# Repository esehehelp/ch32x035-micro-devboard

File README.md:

# CH32X035F7P6 Micro Devboard

CH32X035F7P6 (RISC-V, 48 MHz, 62 KB flash, 20 KB RAM) の小型開発ボード。

## 概要

USB CDC-ACM ライブラリ (`ch32x-cdc`) を中心に、PlatformIO と Arduino IDE の両方をサポート。
ESP32/RP2040 の Arduino Serial と同じ体験 — 初期化を呼ぶだけで USB シリアルが使え、1200bps タッチでファームウェア更新ができる。

## PlatformIO (firmware/)

### 構成

```
firmware/
  platformio.ini          # PlatformIO 設定
  ch32_1k2touch.py        # カスタムアップロードスクリプト
  src/
    main.c                # サンプルアプリ (PC3 blink + CDC echo)
    startup.S             # ベクタテーブル + 起動コード
    link.ld               # リンカスクリプト
  lib/
    ch32x-cdc/
      include/
        ch32x_cdc.h       # 公開 API
        ch32x_regs.h      # MIT レジスタ定義 (WCH HAL 非依存)
      src/
        ch32x_cdc.c       # CDC 実装 (ディスクリプタ, ISR, バッファ)
```

### ビルド & 書き込み

```bash
cd firmware

# ビルド
pio run

# 書き込み (初回: wch-link 経由)
pio run -t upload --upload-port wlink

# 書き込み (2回目以降: USB CDC 1200bps タッチ経由, wch-link 不要)
pio run -t upload
```

初回書き込みは wch-link (SWD) が必要。一度ファームウェアが動けば、以降は USB ケーブルだけで `pio run -t upload` でフラッシュできる。

## Arduino IDE (arduino/)

### インストール

1. `arduino/ch32x035f7p6/` を Arduino のハードウェアディレクトリにコピーまたはシンボリックリンク:
   ```bash
   # Linux
   ln -s $(pwd)/arduino/ch32x035f7p6 ~/.arduino15/packages/ch32x035f7p6

   # または Arduino IDE の「ファイル > 環境設定 > スケッチブックの保存場所」内の
   # hardware/ch32x035f7p6/ に配置
   ```
2. ツールチェイン: WCH の RISC-V GCC (`xpack-riscv-none-embed-gcc`) をパスに追加
3. ボード選択: **CH32X035F7P6** を選択
4. アップロード: 1200bps タッチ + wchisp による自動書き込み

### Arduino API サポート

- `Serial` — USB CDC シリアル (`USBSerial` クラス、`Print` 継承)
- `millis()` / `micros()` / `delay()` / `delayMicroseconds()` — SysTick ベース
- `pinMode()` / `digitalWrite()` / `digitalRead()`

### API

```c
#include "ch32x_cdc.h"

// 初期化 (NULL でデフォルト設定)
ch32x_cdc_config_t cfg = { .magic_baud_enable = 1 };
ch32x_cdc_init(&cfg);

// 読み込み
int ch32x_cdc_available(void);       // 受信バイト数
int ch32x_cdc_read(void);            // 1バイト読み込み (-1 = 空)
size_t ch32x_cdc_read_buf(buf, max); // バッファに一括読み込み

// 書き込み
size_t ch32x_cdc_write(buf, len);    // バイト列送信
size_t ch32x_cdc_print(str);         // 文字列送信
void ch32x_cdc_flush(void);          // TX 完了待ち

// BootROM へリブート (手動呼び出し用)
void ch32x_cdc_reboot_to_bootrom(void);
```

#### 設定

```c
typedef struct {
    int      magic_baud_enable;  // 1200bps リブートトリガ (デフォルト: 有効)
    uint32_t magic_baud;         // トリガボーレート (デフォルト: 1200)
    void (*pre_reboot)(void);    // リブート前コールバック
} ch32x_cdc_config_t;
```

#### RX コールバック

```c
// ISR コンテキストで呼ばれる (weak シンボル、アプリ側でオーバーライド可)
void ch32x_cdc_on_rx(const uint8_t *buf, size_t len) {
    // 受信データを処理
}
```

### サンプルアプリ (PlatformIO)

`firmware/src/main.c` — PC3 LED 点滅 (500ms) + USB CDC エコー。

```c
#include "ch32x_regs.h"
#include "ch32x_cdc.h"

int main(void) {
    ch32x_cdc_init(NULL);

    /* PC3 push-pull output (cdc_init already enabled GPIOC clock) */
    GPIOC->CFGLR = (GPIOC->CFGLR & ~(0xFu << 12)) | (0x3u << 12);

    for (;;) {
        uint8_t buf[64];
        size_t n = ch32x_cdc_read_buf(buf, sizeof(buf));
        if (n > 0)
            ch32x_cdc_write(buf, n);
        ch32x_cdc_poll();
        IWDG->CTLR = 0xAAAA;
    }
}
```

### 技術メモ

- **クロック設定**: `ch32x_cdc_init()` 内で HSI 有効化、Flash 2 wait-state 設定、HPRE=DIV1 (HCLK=48MHz) を行う。BootROM が HPRE を div6 (8MHz) のまま残すため、明示的なクリアが必要。
- **SysTick**: QingKe V4C の 64-bit カウンタ。HCLK/8 (6MHz) で動作。カウンタリセットは CTLR bit 4 で行う（CNTL/CNTH 直接書き込みは不可）。
- **レジスタ定義**: `ch32x_regs.h` は TRM から自作した MIT ライセンスの定義。WCH HAL/EVT に依存しない。
- **割り込み**: `USBFS_IRQHandler` はライブラリが strong シンボルとして提供。`startup.S` の weak シンボルをリンカが解決。
- **ISR 属性**: GCC 8.2 (Arduino/WCH ツールチェイン) では `__attribute__((interrupt))` を使用。`WCH-Interrupt-fast` はカリーセーブドレジスタしか保存しないバグがある。GCC 12 (PlatformIO) では `WCH-Interrupt-fast` で問題なし。
- **BootROM 突入**: `FLASH->BOOT_MODEKEYR` アンロック → `FLASH->STATR |= BOOT_MODE` → PFIC システムリセット。チップ内蔵 ISP (0x1FFF0000) が起動し、wchisp で書き込み可能。
- **USB-C**: PC14/PC15 に CC プルダウンを設定 (USBPD ペリフェラル経由)。ホストが VBUS を供給するために必要。
- **HardFault**: サンプルアプリでは HardFault 時に BootROM へリブート。クラッシュしてもファームウェア書き直し可能。
- **IWDG**: 旧ファームウェアが IWDG を起動していた場合、ソフトウェアリセットでは停止しない。メインループで `IWDG->CTLR = 0xAAAA` で給餌するか、電源を入れ直す。
- **C++ 初期化**: startup.S で `__libc_init_array()` を呼び出し、vtable やグローバルコンストラクタを初期化。`-nostartfiles` 使用時は `_init`/`_fini` スタブも必要。

## License

MIT

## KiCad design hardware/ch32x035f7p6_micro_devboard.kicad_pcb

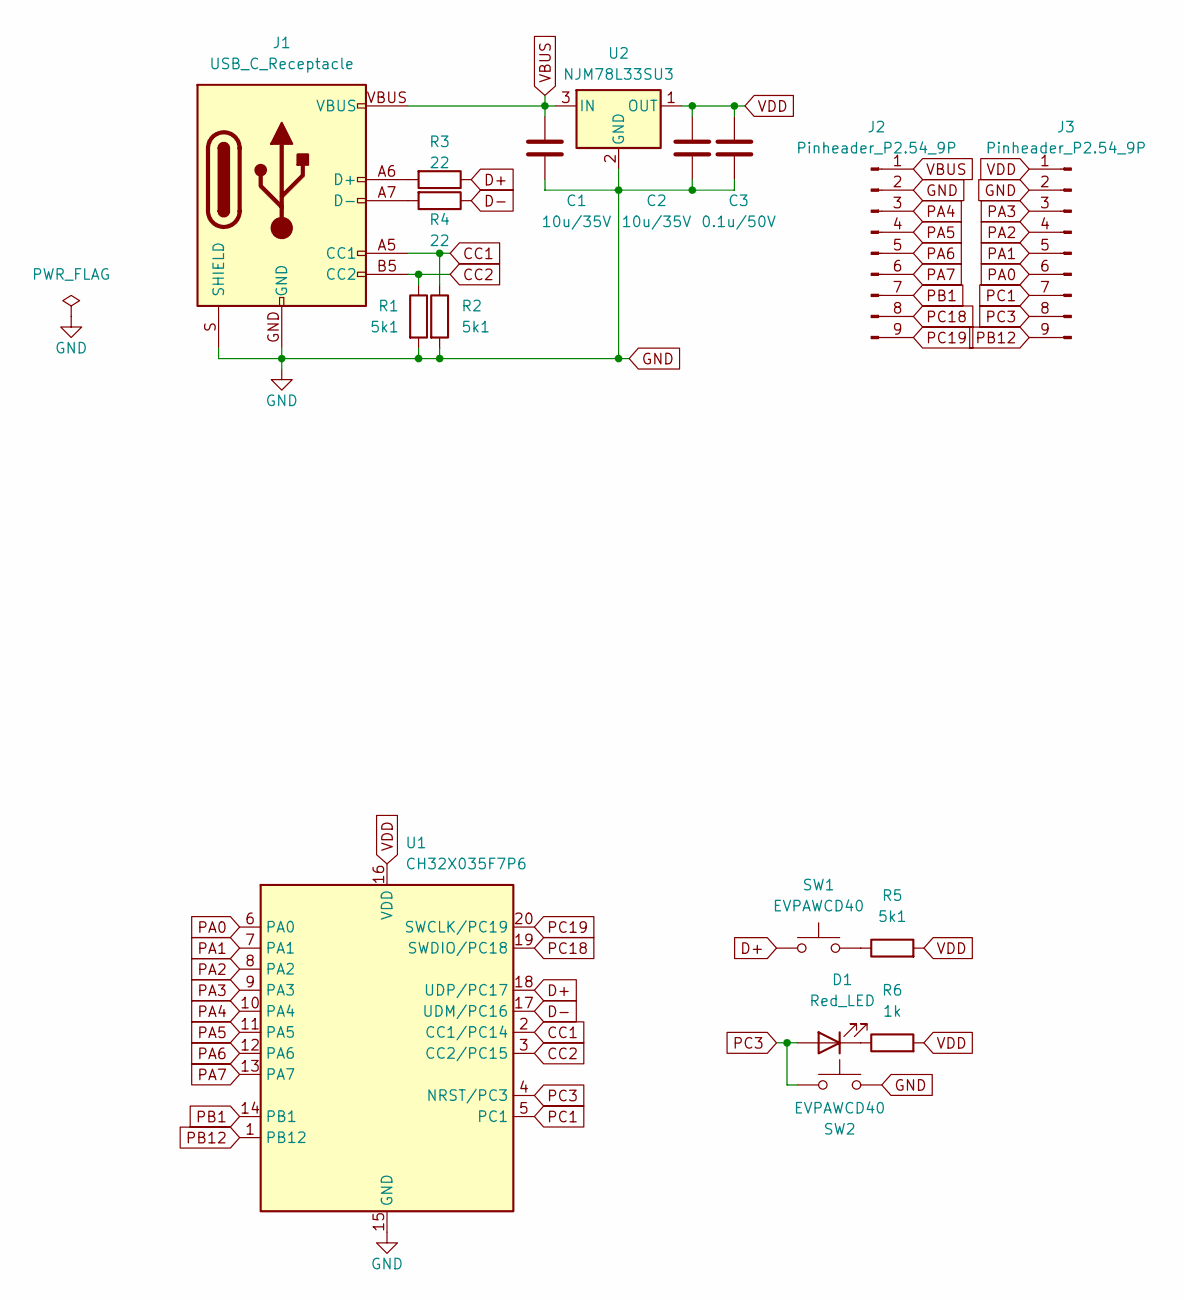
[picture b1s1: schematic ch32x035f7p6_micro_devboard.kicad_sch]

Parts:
C1, C2: 10u/35V; C_0603_1608Metric
C3: 0.1u/50V; C_0603_1608Metric
D1: Red_LED; LED_0603_1608Metric
J1: USB_C_Receptacle; USB-C_16-HandSolder
J2, J3: Pinheader_P2.54_9P; PinHeader_1x09_P2.54mm_Vertical
R1, R2, R5: 5k1; R_0603_1608Metric
R3, R4: 22; R_0603_1608Metric
R6: 1k; R_0603_1608Metric
SW1, SW2: EVPAWCD40; SW_SPST_EVPAW
U1: CH32X035F7P6; TSSOP-20_4.4x6.5mm_P0.65mm
U2: NJM78L33SU3; SOT-89-3

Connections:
CC1: J1.A5 (CC1), R2.1, U1.2 (CC1/PC14)
CC2: J1.B5 (CC2), R1.1, U1.3 (CC2/PC15)
D+: R3.1, SW1.1, U1.18 (UDP/PC17)
D-: R4.1, U1.17 (UDM/PC16)
GND: C1.2, C2.2, C3.2, J1.GND, J1.S (SHIELD), J2.2, J3.2, R1.2, R2.2, SW2.2, U1.15 (GND), U2.2 (GND)
unnamed: D1.1 (K), R6.1
unnamed: J1.A6 (D+), J1.B6 (D+), R3.2
unnamed: J1.A7 (D-), J1.B7 (D-), R4.2
unnamed: R5.1, SW1.2
PA0: J3.6, U1.6 (PA0)
PA1: J3.5, U1.7 (PA1)
PA2: J3.4, U1.8 (PA2)
PA3: J3.3, U1.9 (PA3)
PA4: J2.3, U1.10 (PA4)
PA5: J2.4, U1.11 (PA5)
PA6: J2.5, U1.12 (PA6)
PA7: J2.6, U1.13 (PA7)
PB1: J2.7, U1.14 (PB1)
PB12: J3.9, U1.1 (PB12)
PC1: J3.7, U1.5 (PC1)
PC3: D1.2 (A), J3.8, SW2.1, U1.4 (NRST/PC3)
PC18: J2.8, U1.19 (SWDIO/PC18)
PC19: J2.9, U1.20 (SWCLK/PC19)
VBUS: C1.1, J1.VBUS, J2.1, U2.3 (IN)
VDD: C2.1, C3.1, J3.1, R5.2, R6.2, U1.16 (VDD), U2.1 (OUT)

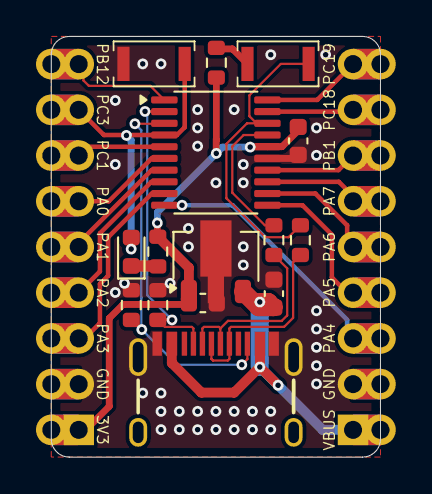
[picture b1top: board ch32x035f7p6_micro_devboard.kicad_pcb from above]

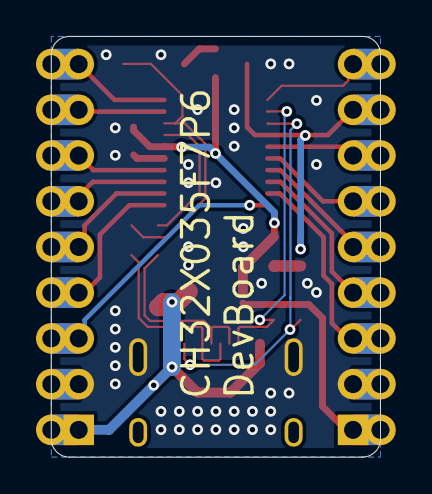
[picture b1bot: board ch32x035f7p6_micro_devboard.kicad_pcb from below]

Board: 2 copper layers, 18.3 x 23.4 mm, 17 parts (2 on the bottom side), 25 nets.

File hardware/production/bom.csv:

Designator,Footprint,Quantity,Value,LCSC Part #
"C1, C2",0603,2,10u/35V,
C3,0603,1,0.1u/50V,
D1,0603,1,Red_LED,
J1,USB-C_16-HandSolder,1,USB_C_Receptacle,
"J2, J3",PinHeader_1x09_P2.54mm_Vertical,2,Pinheader_P2.54_9P,
"R1, R2, R5",0603,3,5k1,
"R3, R4",0603,2,22,
R6,0603,1,1k,
"SW1, SW2",SW_SPST_EVPAW,2,EVPAWCD40,
U1,TSSOP-20_4.4x6.5mm_P0.65mm,1,CH32X035F7P6,
U2,SOT-89-3,1,NJM78L33SU3,

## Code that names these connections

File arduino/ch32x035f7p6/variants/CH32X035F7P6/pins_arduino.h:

/*
 * pins_arduino.h — Pin mapping for CH32X035F7P6 Micro Devboard.
 *
 * CH32X035F7P6 (TSSOP20) available GPIO:
 *   PA0-PA7, PB1, PB12, PC1, PC3, PC18(SWDIO), PC19(SWCLK)
 *   PC14/15/16/17 reserved for USB CDC (CC1, CC2, D-, D+)
 *
 * SPDX-License-Identifier: MIT
 */
#ifndef pins_arduino_h
#define pins_arduino_h

#define NUM_DIGITAL_PINS    14
#define NUM_ANALOG_INPUTS   8

/* D11 = PC3 = devboard LED */
#define LED_BUILTIN         11

/*
 * Arduino pin  ->  GPIO
 *   D0  = PA0       (A0)
 *   D1  = PA1       (A1)
 *   D2  = PA2       (A2)
 *   D3  = PA3       (A3)
 *   D4  = PA4       (A4)
 *   D5  = PA5       (A5)
 *   D6  = PA6       (A6)
 *   D7  = PA7       (A7)
 *   D8  = PB1
 *   D9  = PB12
 *   D10 = PC1
 *   D11 = PC3       (LED)
 *   D12 = PC18      (SWDIO — usable as GPIO)
 *   D13 = PC19      (SWCLK — usable as GPIO)
 */

/* Analog pin aliases */
#define A0  0
#define A1  1
#define A2  2
#define A3  3
#define A4  4
#define A5  5
#define A6  6
#define A7  7

#endif /* pins_arduino_h */
